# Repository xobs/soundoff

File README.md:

# Soundoff

Turn off power and data to the USB-C port when the connected host is in suspend.

This device is designed to be built with the cheapest process at JLCPCB.

It requires [firmware to be loaded](https://github.com/xobs/soundoff-firmware).

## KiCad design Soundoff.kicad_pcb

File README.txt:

# Soundoff

Turn off USB power when the device is in suspend.

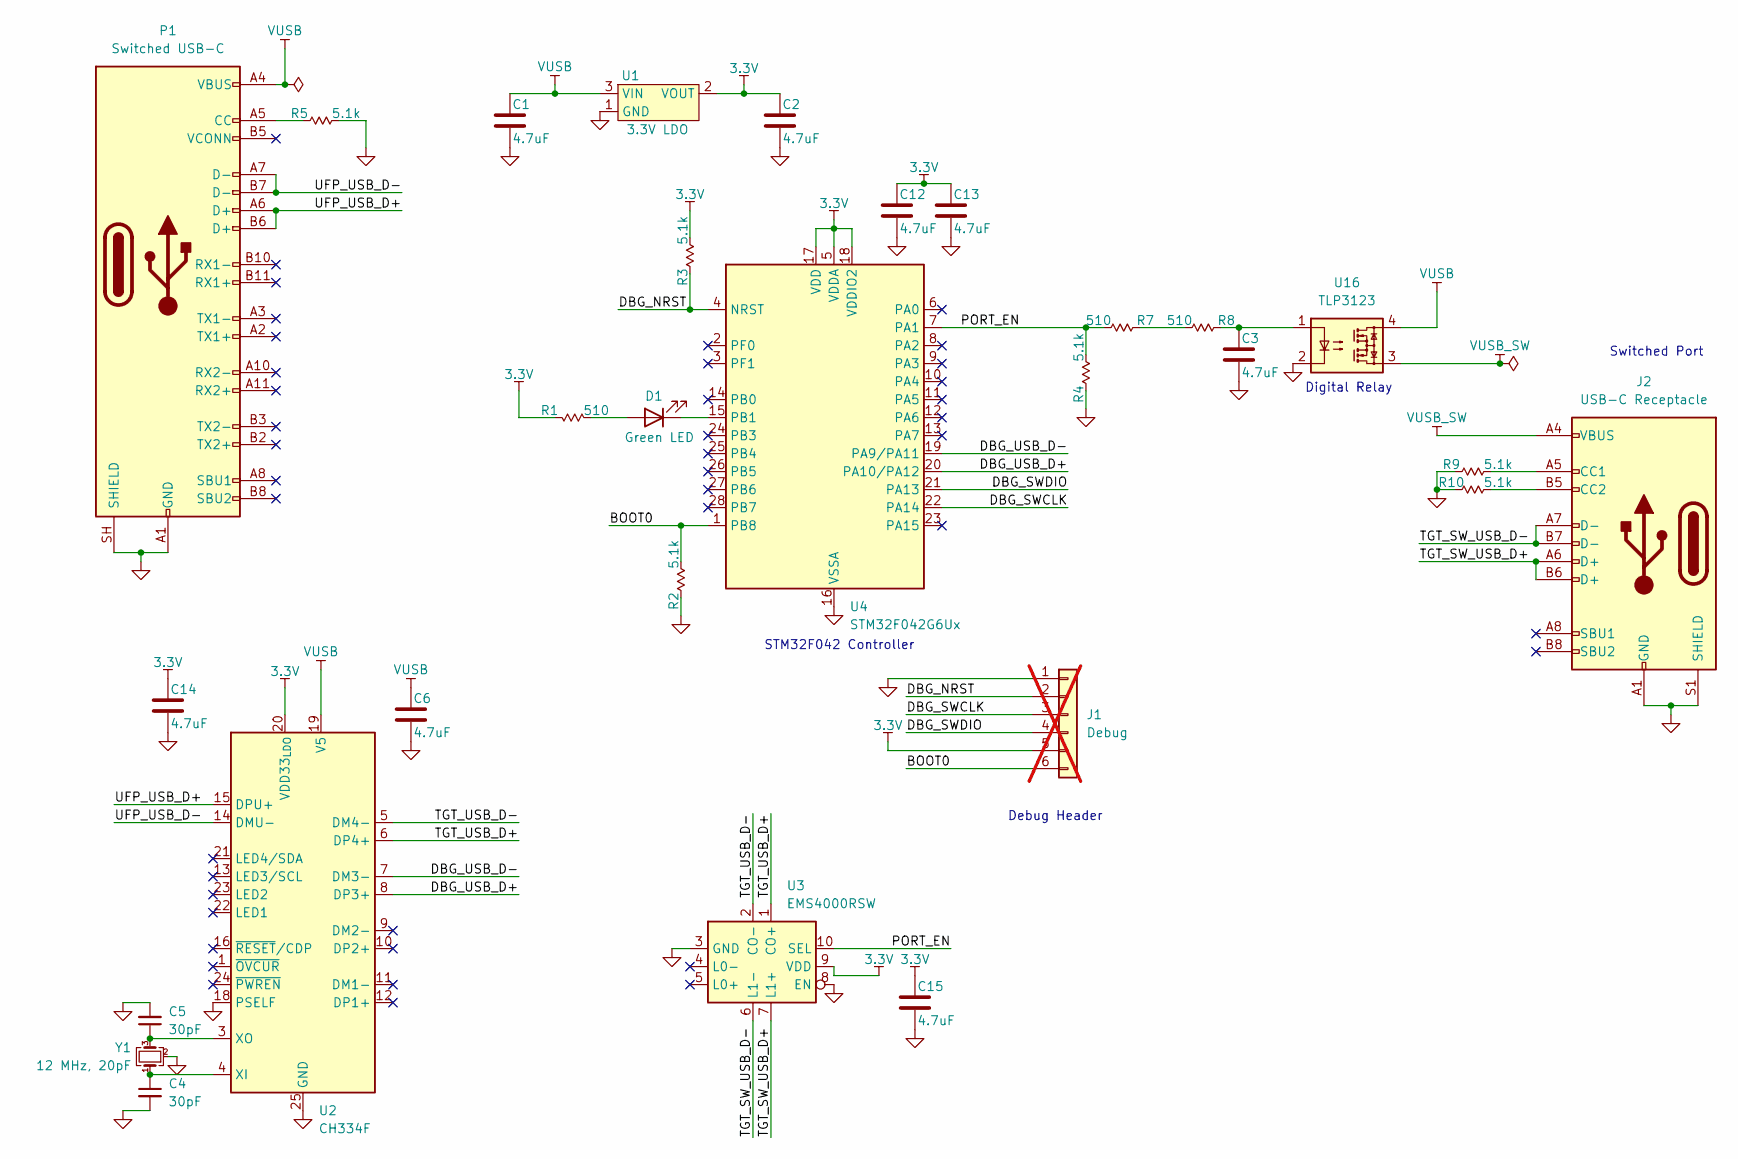
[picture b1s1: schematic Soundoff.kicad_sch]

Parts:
C1, C2, C3, C6, C12, C13, C14, C15: 4.7uF; C_0402_1005Metric; MPN CL05A475MP5NRNC; LCSC C23733
C4, C5: 30pF; C_0603_1608Metric; MPN 0603CG300J500NT; LCSC C1658
D1: Green LED; LED_0805_2012Metric; MPN KT-0805G; LCSC C2297
J1: Debug; PinHeader_1x06_P2.54mm_Vertical; not fitted
J2: USB-C Receptacle; USB_C_Receptacle_HRO_TYPE-C-31-M-12; MPN TYPE-C 16PIN 2MD(073); LCSC C2765186
P1: Switched USB-C; USB-C-SMD_TYPE-C-31-G-07-1; MPN 13001-UCAM001-X; LCSC C3148223
R1, R7, R8: R 510 0402; R_0402_1005Metric; MPN 0402WGF5100TCE; LCSC C25123
R2, R3, R4, R5, R9, R10: R 5.1k 0402; R_0402_1005Metric; MPN 0402WGF5101TCE; LCSC C25905
U1: 3.3V LDO; SOT-23-3; MPN XC6206P332MR-G; LCSC C5446
U2: CH334F; QFN-24-1EP_4x4mm_P0.5mm_EP2.7x2.7mm; MPN CH334F; LCSC C5187527
U3: EMS4000RSW; QFN-10_1.4x1.8_Pitch0.4mm; MPN EMS4000RSW; LCSC C49186227
U4: STM32F042G6Ux; QFN-28_4x4mm_P0.5mm; MPN STM32F042G6U6; LCSC C961597
U16: TLP3123; SO-4_4.4x3.9mm_P2.54mm; MPN TLP3123; LCSC C20624244
Y1: 12 MHz, 20pF; Crystal_SMD_3225-4Pin_3.2x2.5mm; MPN X322512MSB4SI; LCSC C9002

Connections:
3.3V: C2.1, C12.1, C13.1, C14.1, C15.1, J1.5, R1.1, R3.1, U1.2 (VOUT), U2.20 (VDD33_{LDO}), U3.9 (VDD), U4.5 (VDDA), U4.17 (VDD), U4.18 (VDDIO2)
/BOOT0: J1.6, R2.1, U4.1 (PB8)
/DBG_NRST: J1.2, R3.2, U4.4 (NRST)
/DBG_SWCLK: J1.3, U4.22 (PA14)
/DBG_SWDIO: J1.4, U4.21 (PA13)
/DBG_USB_D+: U2.8 (DP3+), U4.20 (PA10/PA12)
/DBG_USB_D-: U2.7 (DM3-), U4.19 (PA9/PA11)
/PORT_EN: R4.1, R7.2, U3.10 (SEL), U4.7 (PA1)
/TGT_SW_USB_D+: J2.A6 (D+), J2.B6 (D+), U3.7 (L1+)
/TGT_SW_USB_D-: J2.A7 (D-), J2.B7 (D-), U3.6 (L1-)
/TGT_USB_D+: U2.6 (DP4+), U3.1 (CO+)
/TGT_USB_D-: U2.5 (DM4-), U3.2 (CO-)
/UFP_USB_D+: P1.A6 (D+), P1.B6 (D+), U2.15 (DPU+)
/UFP_USB_D-: P1.A7 (D-), P1.B7 (D-), U2.14 (DMU-)
GND: C1.2, C2.2, C3.2, C4.2, C5.2, C6.2, C12.2, C13.2, C14.2, C15.2, J1.1, J2.A1 (GND), J2.A12 (GND), J2.B1 (GND), J2.B12 (GND), J2.S1 (SHIELD), P1.A1 (GND), P1.A12 (GND), P1.B1 (GND), P1.B12 (GND), P1.SH (SHIELD), R2.2, R4.2, R5.1, R9.2, R10.2, U1.1 (GND), U2.18 (PSELF), U2.25 (GND), U3.3 (GND), U3.8 (EN), U4.16 (VSSA), U16.2, Y1.2 (G), Y1.4 (G)
unnamed: C3.1, R8.1, U16.1
unnamed: D1.2 (A), R1.2
unnamed: D1.1 (K), U4.15 (PB1)
unnamed: J2.A5 (CC1), R9.1
unnamed: J2.B5 (CC2), R10.1
unnamed: P1.A5 (CC), R5.2
unnamed: R7.1, R8.2
unnamed: C4.1, U2.4 (XI), Y1.1
unnamed: C5.1, U2.3 (XO), Y1.3
VUSB: C1.1, C6.1, P1.A4 (VBUS), P1.A9 (VBUS), P1.B4 (VBUS), P1.B9 (VBUS), U1.3 (VIN), U2.19 (V5), U16.4
VUSB_SW: J2.A4 (VBUS), J2.A9 (VBUS), J2.B4 (VBUS), J2.B9 (VBUS), U16.3

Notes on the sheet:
STM32F042 Controller
Switched Port
Debug Header
Digital Relay

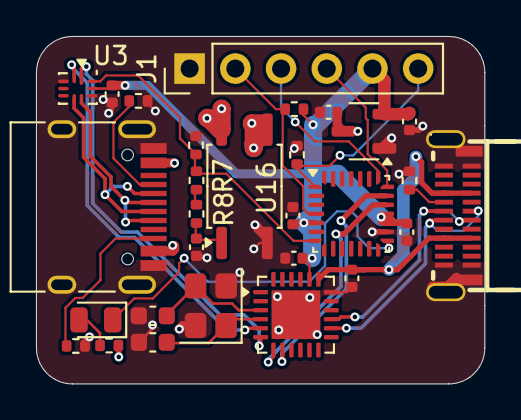
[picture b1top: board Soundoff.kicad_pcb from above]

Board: 4 copper layers, 24.9 x 19.3 mm, 29 parts (0 on the bottom side), 26 nets.

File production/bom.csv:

Designator,Footprint,Quantity,Value,LCSC Part #
"C1, C12, C13, C14, C15, C2, C3, C6",0402,8,4.7uF,C23733
"C4, C5",0603,2,30pF,C1658
D1,0805,1,Green LED,C2297
J2,USB_C_Receptacle_HRO_TYPE-C-31-M-12,1,USB-C Receptacle,C2765186
P1,USB-C-SMD_TYPE-C-31-G-07-1,1,Switched USB-C,C3148223
"R1, R7, R8",0402,3,R 510 0402,C25123
"R10, R2, R3, R4, R5, R9",0402,6,R 5.1k 0402,C25905
U1,SOT-23-3,1,3.3V LDO,C5446
U16,SO-4_4.4x3.9mm_P2.54mm,1,TLP3123,C20624244
U2,QFN-24-1EP_4x4mm_P0.5mm_EP2.7x2.7mm,1,CH334F,C5187527
U3,QFN-10_1.4x1.8_Pitch0.4mm,1,EMS4000RSW,C49186227
U4,QFN-28_4x4mm_P0.5mm,1,STM32F042G6Ux,C961597
Y1,Crystal_SMD_3225-4Pin_3.2x2.5mm,1,"12 MHz, 20pF",C9002

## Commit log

2025-11-12 readme: add information on firmware
2026-06-01 v2: make usb-c and pass data through
2026-06-02 v3: fix usb polarity
    The USB polarity was incorrect -- the DFP and UFP roles were swapped.
    Change the connectors around to make it correct now.
